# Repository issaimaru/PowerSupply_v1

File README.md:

# アズサ(Azusa)

<br>

<br>
この基板はJLCPCB様のFree PCB Sponsorshipにて制作しています．<br>

## Overview
  [MotorDriver-Controller_v4](https://github.com/TNCT-Mechatech/MotorDriver-Controller_v4)の機能+αと電源回路を合体させた統合型電源基板<br>
 
## Environments
&emsp;
&emsp;&emsp;
<br>

## Usage

1. [DriveUnit Bseries](https://github.com/Issaimaru/MoterDriver_v1)を使用したいチャネルのカードエッジコネクタに差し込む．<br>
1. モータードライバを差し込んだエッジコネクタと同じチャネルにモータを接続し，必要に応じて同じチャネルのコネクタにロータリーエンコーダを接続する．<br>
1. 非常停止スイッチを刺したコネクタの下にあるトグルスイッチをONに，それ以外のトグルスイッチをOFFにする．
1. XT90とUSB Type-Cからそれぞれ電源を供給し，非常停止スイッチをONにすると稼働する．
> **Note**<br>
> USB Type-C用電源を省略する方法はDescriptionsを参照<br>

## Features
<dl>
  <dt>通信プロトコル</dt>
  <dd>CAN with Flexible Data Rate(CAN FD)</dd>
  <dt>通信用コネクタ・ケーブル</dt>
  <dd>RJ-45/LANケーブル</dd>
  <dt>マイクロコンピュータ</dt>
  <dd>STM32F446RE</dd>
  <dt>特殊回路</dt>
  <dd>
  ・オートディスチャージ回路<br>
  ・車載用スローブローヒューズ

  <dt>保護回路(電源側)</dt>
  <dd>
  ・過電流保護(閾値可変)<br>
  ・ヒステリシス付き過熱保護<br>
  ・短絡保護<br>
  ・突入電流抑制<br>
  </dd>
  <dt>保護回路(信号側)</dt>
  <dd>
  ・過電圧保護<br>
  ・過電圧クランプ<br>
  ・突入電流抑制<br>
  ・過電流保護(東芝のeFuseを使用)<br>
  ・過熱保護<br>

## Descriptions
本ハードウェアの使用方法を詳しく書いていきます．<br>
質問や連絡等あれば[@TakenMaker](https://twitter.com/TakenMaker)までお願いします．<br>

### 回路図
&ensp;&ensp;

#### 始動方法
始動方法については[Usage](#usage)で示しました．<br>
ここでは始動時の応用的な使い方について紹介していきます．

- 信号用バッテリーの省略

<br>

JP6で信号用の電源をUSB給電or外部給電に切り替えることができます．<br>
外部電源としては，SPOWのピンに接続された電源かリポバッテリーか選ぶことができます．<br>
リポバッテリーの場合は「GND」と「SPOW」のピンヘッダを短絡してください．<br>
その際にE5VのLEDが点灯していることを確認してください．

## Bills of materials
> **Note**<br>
>最低限の部品のみここに書いています．<br>
>はんだ付けに必要な部品を調べるときは以下のexcelファイルを見るか，BOMファイルを出力してください．<br>
>[アズサ(Azusa)-ver2.0_必要部品.xlsx](src/%E3%82%A2%E3%82%BA%E3%82%B5(Azusa)-ver2.0_%E5%BF%85%E8%A6%81%E9%83%A8%E5%93%81.xlsx)
<br>
<dl>
  <dt>マイクロコンピュータ</dt>
  <dd>

  [STM32F446RET6](https://www.digikey.jp/ja/products/detail/stmicroelectronics/STM32F446RET6/5175962)

  </dd>

  <dt>電流センサ</dt>
  <dd>
  
  [CZ-3A04](https://www.digikey.jp/ja/products/detail/asahi-kasei-microdevices-akm/CZ3A04/11570562)

  </dd>
  <dt>CANトランシーバ</dt>
  <dd>

  [MCP2558FDT-H/MNY](https://www.digikey.jp/ja/products/detail/microchip-technology/MCP2558FDT-H-MNY/6009304)

  </dd>
  <dt>CANコントローラ</dt>
  <dd>

  [MCP2517FDT-H/SL](https://www.digikey.jp/ja/products/detail/microchip-technology/MCP2517FDT-H-SL/7801797)

  </dd>
  <dt>ヒートシンク</dt>
  <dd>
  
  [V2020B](https://www.digikey.jp/ja/products/detail/assmann-wsw-components/V2020B/8826902)
  
  </dd>
  <dt>ヒューズ</dt>
  <dd>

  [0297030.WXT](https://www.digikey.jp/en/products/detail/littelfuse-inc/0297030-WXT/5233697)

  </dd>
  <dt>USB・シリアル変換IC</dt>
  <dd>

  [CH340E](https://akizukidenshi.com/catalog/g/gI-13543/)

  </dd>
  <dt>NTCサーミスタ</dt>
  <dd>

  [NCU15WB473F60RC](https://www.digikey.jp/ja/products/detail/murata-electronics/NCU15WB473F60RC/9686720)

  </dd>
  <dt>DIPスイッチ</dt>
  <dd>

  [RDS-16S-1055-SMT-TR](https://www.digikey.jp/ja/products/detail/cui-devices/RDS-16S-1055-SMT-TR/12424507)

  </dd>
</dl>

## Contact
- Twitter [@TakenMaker](https://twitter.com/TakenMaker)

## Author
    
<table>
  <tr>
    <td align="center"><a href="https://github.com/Issaimaru"><br /></a>Issaimaru</td>
  </tr>
</table>
    
## Licence
  - Copyright © 2022-2023 Issaimaru<br>

本ハードウェアは，Apache License Version 2.0の下で配布されます．<br>
詳しくはLICENSEファイルをご確認ください．<br>

## 回路図のダウンロード(クローン)方法
1. Gitをインストールする．<br>Gitのインストール方法は[ここ](https://www.sejuku.net/blog/73444)を参照．
1. コマンドプロンプトを立ち上げる．
1. `cd ”ダウンロード先フォルダの絶対パス” `<br>
1. `git clone https://github.com/Issaimaru/PowerSupply_v1.git`<br>

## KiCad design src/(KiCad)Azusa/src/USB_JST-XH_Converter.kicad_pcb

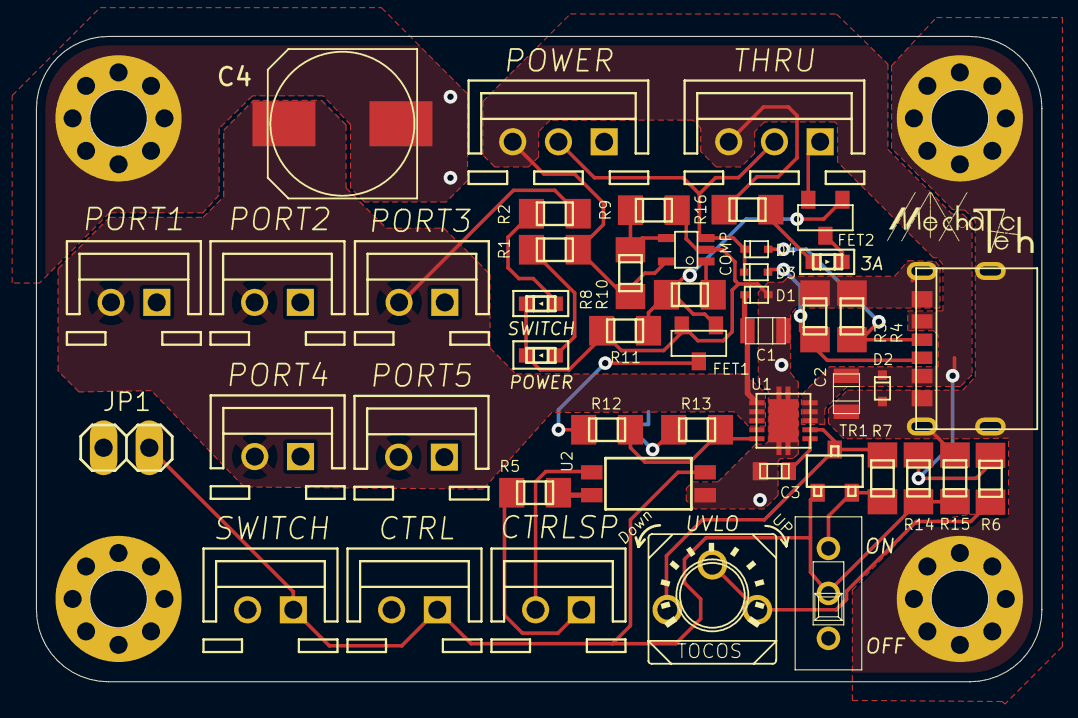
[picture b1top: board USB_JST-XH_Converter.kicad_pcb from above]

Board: 2 copper layers, 55.9 x 35.9 mm, 51 parts (0 on the bottom side), 22 nets.

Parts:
C1, C2: GRM21BC72A105KE01
C3: GRM1885C1H242JA01D; GRM18
C4: UWT1E221MNL1GS
COMP1: MCP6541T-I_LT; SC-70-5
CTRL: 02-JST; B2B-XH
CTRLSP: 02-JST; B2B-XH
D1, D3, D4: RB751S40; SOD-523
D2: PJSD12TS; SOD-523
FET1, FET2: BSS138; SOT-23
H1, H2, H3, H4: MOUNT-HOLE3.2(NORESIST); 3,2
JP1: PINHD-1X2; 1X02
LED1: SML-E12V8WT86
PORT1, PORT2, PORT3, PORT4, PORT5: 02-JST; B2B-XH
POW1: SML-E12V8WT86
POWER: 03-JST; B3B-XH
R1, R2: RG2012N-101-B-T5; RG2012
R3, R4: 5.1k; RG2012
R5: 1k; RG2012
R6, R8, R13#2, R14: 10k; RG2012
R7: 3k; RG2012
R9: 2.7k; RG2012
R12: 69.8k; RG2012
R12#2: 10; RG2012
R13: 75k; RG2012
R16: 100k; RG2012
R18: 100; RG2012
SW1: SS-12D00G3
SW2: SML-E12V8WT86
SWITCH: 02-JST; B2B-XH
THRU: 03-JST; B3B-XH
TP1: GF063PB302K; GF063PB104K
TR1: 2SC3325
U1: TCKE805NAWSON10B_TOS-REC; WSON10B_TOS-RIC
U2: TLP293; SO4_TOS
USB1: UJC-HP-3-SMT-TR

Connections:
CC: COMP1.IN+, D3.C, D4.C, POWER.2, THRU.2
CC1: D3.A, R3.LEFT, USB1.A5
CC2: D4.A, R4.LEFT, USB1.B5
GND: C1.P$2, C2.P$2, C3.R, C4.C, COMP1.VSS, D1.A, D2.A, FET1.S, FET2.S, H1.P$1, H2.P$1, H3.P$1, H4.P$1, JP1.2, PORT1.1, PORT2.1, PORT3.1, PORT4.1, PORT5.1, POW1.K, POWER.1, R3.RIGHT, R4.RIGHT, R7.LEFT, R9.RIGHT, R13.RIGHT, R13#2.RIGHT, R16.RIGHT, SW1.R, SW2.K, SWITCH.2, THRU.1, TR1.E, U1.GND1, U1.GND2, U1.GND3, U1.GND4, U1.GND5, U2.3, USB1.A12, USB1.B12, USB1.SHIELD1, USB1.SHIELD2, USB1.SHIELD3, USB1.SHIELD4
ILIM: R12.LEFT, R13.LEFT, U1.ILIM
unnamed: C3.L, U1.DVDT
unnamed: COMP1.IN-, R8.LEFT, R9.LEFT
unnamed: COMP1.OUT, R12#2.RIGHT
unnamed: CTRLSP.1, R5.RIGHT
unnamed: CTRLSP.2, U2.1
unnamed: FET1.D, R12.RIGHT
unnamed: FET2.D, LED1.K
unnamed: LED1.A, R18.RIGHT
unnamed: POW1.A, R1.LEFT
unnamed: R2.LEFT, SW2.A
unnamed: R5.LEFT, U2.2
unnamed: R6.LEFT, TP1.CENTER, TP1.RIGHT
unnamed: R7.RIGHT, TP1.LEFT, TR1.C, U1.EN/UVLO
OUT: FET1.G, FET2.G, R12#2.LEFT, R13#2.LEFT
SWITCH: CTRL.1, JP1.1, R14.LEFT, R16.LEFT, SW1.C, SWITCH.1, TR1.B, U2.4
VCC: C1.P$1, C4.A, D1.C, PORT1.2, PORT2.2, PORT3.2, PORT4.2, PORT5.2, R2.RIGHT, U1.VOUT1, U1.VOUT2, U1.VOUT3
VCC_P: C2.P$1, COMP1.VDD, D2.C, POWER.3, R1.RIGHT, R6.RIGHT, R8.RIGHT, R14.RIGHT, R18.LEFT, THRU.3, U1.VIN1, U1.VIN2, U1.VIN3, USB1.A9, USB1.B9

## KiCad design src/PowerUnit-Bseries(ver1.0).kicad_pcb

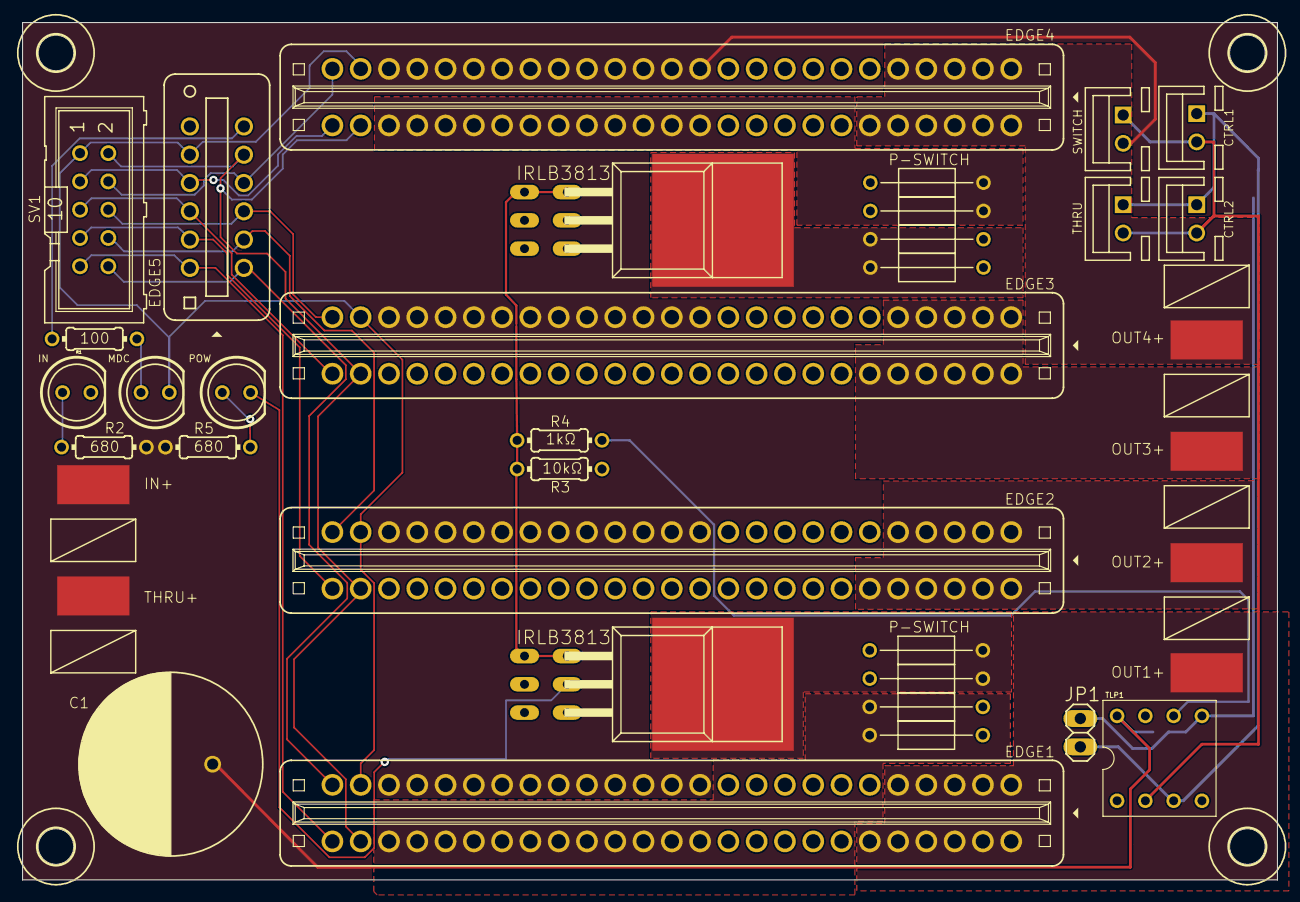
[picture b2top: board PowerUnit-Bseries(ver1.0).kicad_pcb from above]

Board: 2 copper layers, 112.7 x 77.0 mm, 50 parts (0 on the bottom side), 37 nets.

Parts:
C1: 50ZLH1000MEFC16X25
C2: GCM188L81H104KA57
CTRL1, CTRL2: 02-JST; B2B-XH
EDGE1, EDGE2, EDGE3, EDGE4: 10046971-019LF-FEMAL; 10046971-019LF
EDGE5: 7-5530843-6
H1, H2, H3, H4: MOUNT-HOLE3.2; 3,2
IN+: PADS14; AWG14
IN-: PADS14; AWG14
IRLB3813, IRLB3813#2, IRLB3813#3, IRLB3813#4: IRLB3813_2; TO-220AB-PUT
JP1: PINHD-1X2; 1X02
LED1, LED2, LED3: LED5MM
OUT1+, OUT1-, OUT2+, OUT2-, OUT3+, OUT3-, OUT4+, OUT4-: PADS14; AWG14
P-1, P-2, P-3, P-4, P-5, P-6, P-7, P-8: P-SWITCH
R1: 100; 0204_7
R2, R5: 680; 0204_7
R3: 1kΩ; 0204_7
R4: 10kΩ; 0204_7
SV1: ML10
SWITCH: 02-JST; B2B-XH
THRU: 02-JST; B2B-XH
THRU+: PADS14; AWG14
THRU-: PADS14; AWG14
TLP1: 2227MC-08-03

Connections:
/DIR1: EDGE1.P$26, EDGE5.P$12, SV1.9
/DIR2: EDGE2.P$26, EDGE5.P$11, SV1.7
/DIR3: EDGE3.P$26, EDGE5.P$10, SV1.5
/DIR4: EDGE4.P$26, EDGE5.P$9, SV1.3
/GND2: EDGE1.P$24, EDGE2.P$24, EDGE3.P$24, EDGE4.P$24, EDGE5.P$8, LED2.K, SV1.1
/LED: EDGE5.P$6, R1.1
/PWM1: EDGE1.P$25, EDGE5.P$1, SV1.10
/PWM2: EDGE2.P$25, EDGE5.P$2, SV1.8
/PWM3: EDGE3.P$25, EDGE5.P$3, SV1.6
/PWM4: EDGE4.P$25, EDGE5.P$4, SV1.4
/VCC2: EDGE1.P$27, EDGE2.P$27, EDGE3.P$27, EDGE4.P$27, EDGE5.P$5, SV1.2
GND: C1.C, C2.P$2, IN-.P$1, IRLB3813.S, IRLB3813#2.S, IRLB3813#3.S, IRLB3813#4.S, JP1.1, LED1.K, R4.2, THRU-.P$1, TLP1.P$5
unnamed: CTRL1.1, CTRL2.1, JP1.2, THRU.1, TLP1.P$3
unnamed: CTRL1.2, CTRL2.2, SWITCH.1, THRU.2, TLP1.P$2
unnamed: EDGE1.P$1, EDGE1.P$2, EDGE1.P$3, EDGE1.P$4, EDGE1.P$5, EDGE1.P$45, EDGE1.P$46, EDGE1.P$47, EDGE1.P$48, EDGE1.P$49, EDGE1.P$50, OUT1+.P$1
unnamed: EDGE1.P$6, EDGE1.P$7, EDGE1.P$8, EDGE1.P$9, EDGE1.P$10, EDGE1.P$11, EDGE1.P$40, EDGE1.P$41, EDGE1.P$42, EDGE1.P$43, EDGE1.P$44, OUT1-.P$1
unnamed: EDGE1.P$28, EDGE1.P$29, EDGE1.P$30, EDGE1.P$31, EDGE1.P$32, EDGE1.P$33, EDGE1.P$34, EDGE1.P$35, EDGE1.P$36, EDGE1.P$37, EDGE1.P$38, EDGE1.P$39, P-1.P$1, P-2.P$1
unnamed: EDGE2.P$1, EDGE2.P$2, EDGE2.P$3, EDGE2.P$4, EDGE2.P$5, EDGE2.P$45, EDGE2.P$46, EDGE2.P$47, EDGE2.P$48, EDGE2.P$49, EDGE2.P$50, OUT2+.P$1
unnamed: EDGE2.P$6, EDGE2.P$7, EDGE2.P$8, EDGE2.P$9, EDGE2.P$10, EDGE2.P$11, EDGE2.P$40, EDGE2.P$41, EDGE2.P$42, EDGE2.P$43, EDGE2.P$44, OUT2-.P$1
unnamed: EDGE2.P$28, EDGE2.P$29, EDGE2.P$30, EDGE2.P$31, EDGE2.P$32, EDGE2.P$33, EDGE2.P$34, EDGE2.P$35, EDGE2.P$36, EDGE2.P$37, EDGE2.P$38, EDGE2.P$39, P-3.P$1, P-4.P$1
unnamed: EDGE3.P$1, EDGE3.P$2, EDGE3.P$3, EDGE3.P$4, EDGE3.P$5, EDGE3.P$45, EDGE3.P$46, EDGE3.P$47, EDGE3.P$48, EDGE3.P$49, EDGE3.P$50, OUT3+.P$1
unnamed: EDGE3.P$6, EDGE3.P$7, EDGE3.P$8, EDGE3.P$9, EDGE3.P$10, EDGE3.P$11, EDGE3.P$40, EDGE3.P$41, EDGE3.P$42, EDGE3.P$43, EDGE3.P$44, OUT3-.P$1
unnamed: EDGE3.P$28, EDGE3.P$29, EDGE3.P$30, EDGE3.P$31, EDGE3.P$32, EDGE3.P$33, EDGE3.P$34, EDGE3.P$35, EDGE3.P$36, EDGE3.P$37, EDGE3.P$38, EDGE3.P$39, P-5.P$1, P-6.P$1
unnamed: EDGE4.P$1, EDGE4.P$2, EDGE4.P$3, EDGE4.P$4, EDGE4.P$5, EDGE4.P$45, EDGE4.P$46, EDGE4.P$47, EDGE4.P$48, EDGE4.P$49, EDGE4.P$50, OUT4+.P$1
unnamed: EDGE4.P$6, EDGE4.P$7, EDGE4.P$8, EDGE4.P$9, EDGE4.P$10, EDGE4.P$11, EDGE4.P$40, EDGE4.P$41, EDGE4.P$42, EDGE4.P$43, EDGE4.P$44, OUT4-.P$1
unnamed: EDGE4.P$28, EDGE4.P$29, EDGE4.P$30, EDGE4.P$31, EDGE4.P$32, EDGE4.P$33, EDGE4.P$34, EDGE4.P$35, EDGE4.P$36, EDGE4.P$37, EDGE4.P$38, EDGE4.P$39, P-7.P$1, P-8.P$1
unnamed: IRLB3813.G, IRLB3813#2.G, IRLB3813#3.G, IRLB3813#4.G, R3.2, R4.1
unnamed: IRLB3813.P$1, P-1.P$2, P-2.P$2
unnamed: IRLB3813#2.D, LED3.K
unnamed: IRLB3813#2.P$1, P-3.P$2, P-4.P$2
unnamed: IRLB3813#3.P$1, P-5.P$2, P-6.P$2
unnamed: IRLB3813#4.P$1, P-7.P$2, P-8.P$2
unnamed: LED1.A, R2.1
unnamed: LED2.A, R1.2
unnamed: LED3.A, R5.1
unnamed: R3.1, TLP1.P$6
VCC: C1.A, C2.P$1, EDGE1.P$12, EDGE1.P$13, EDGE1.P$14, EDGE1.P$15, EDGE1.P$16, EDGE1.P$17, EDGE1.P$18, EDGE1.P$19, EDGE1.P$20, EDGE1.P$21, EDGE1.P$22, EDGE1.P$23, EDGE2.P$12, EDGE2.P$13, EDGE2.P$14, EDGE2.P$15, EDGE2.P$16, EDGE2.P$17, EDGE2.P$18, EDGE2.P$19, EDGE2.P$20, EDGE2.P$21, EDGE2.P$22, EDGE2.P$23, EDGE3.P$12, EDGE3.P$13, EDGE3.P$14, EDGE3.P$15, EDGE3.P$16, EDGE3.P$17, EDGE3.P$18, EDGE3.P$19, EDGE3.P$20, EDGE3.P$21, EDGE3.P$22, EDGE3.P$23, EDGE4.P$12, EDGE4.P$13, EDGE4.P$14, EDGE4.P$15, EDGE4.P$16, EDGE4.P$17, EDGE4.P$18, EDGE4.P$19, EDGE4.P$20, EDGE4.P$21, EDGE4.P$22, EDGE4.P$23, IN+.P$1, R2.2, R5.2, SWITCH.2, THRU+.P$1, TLP1.P$8

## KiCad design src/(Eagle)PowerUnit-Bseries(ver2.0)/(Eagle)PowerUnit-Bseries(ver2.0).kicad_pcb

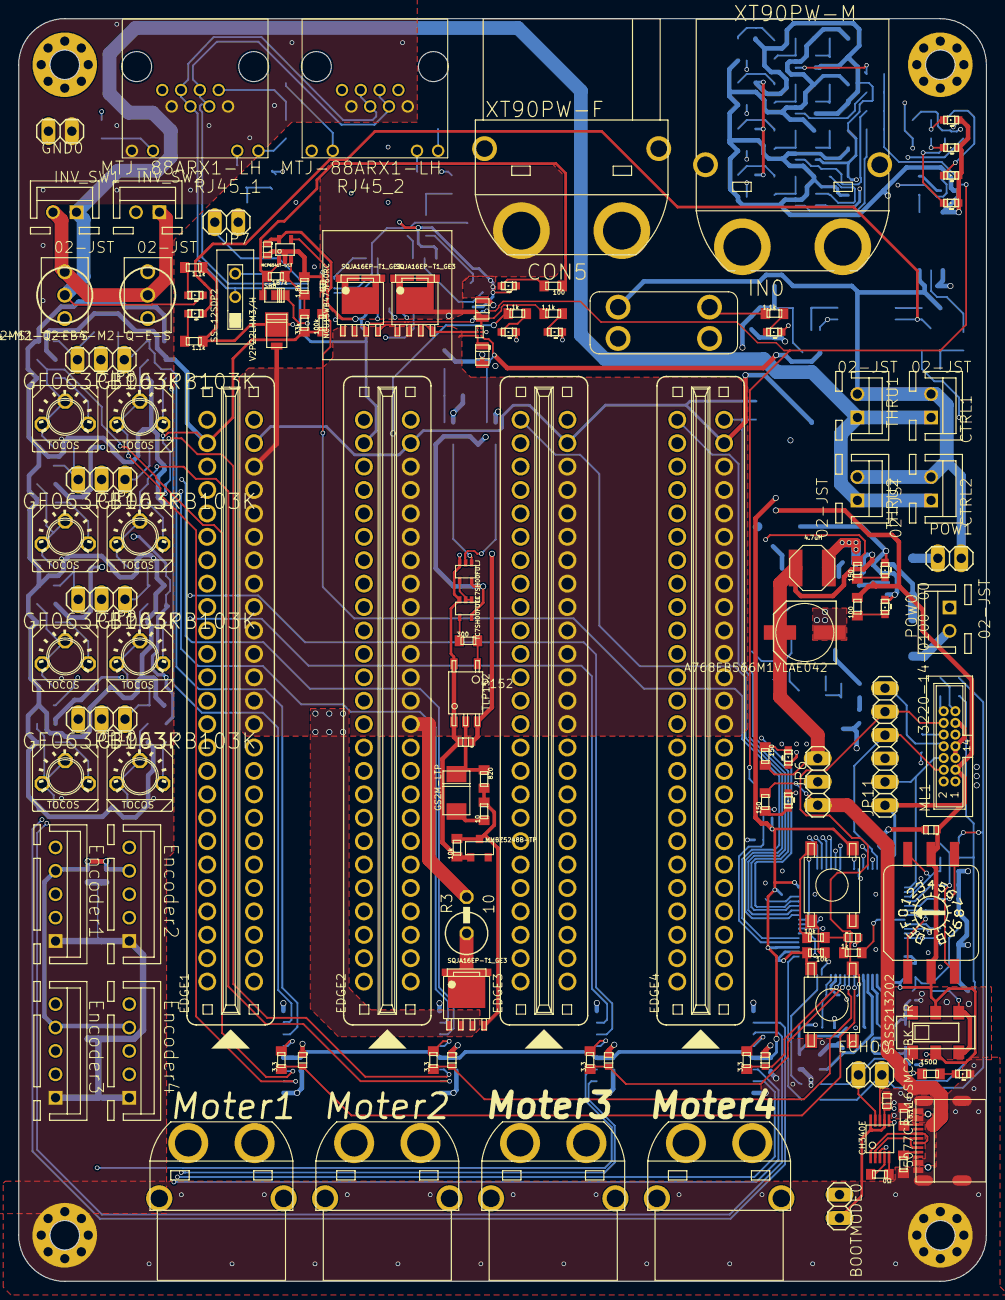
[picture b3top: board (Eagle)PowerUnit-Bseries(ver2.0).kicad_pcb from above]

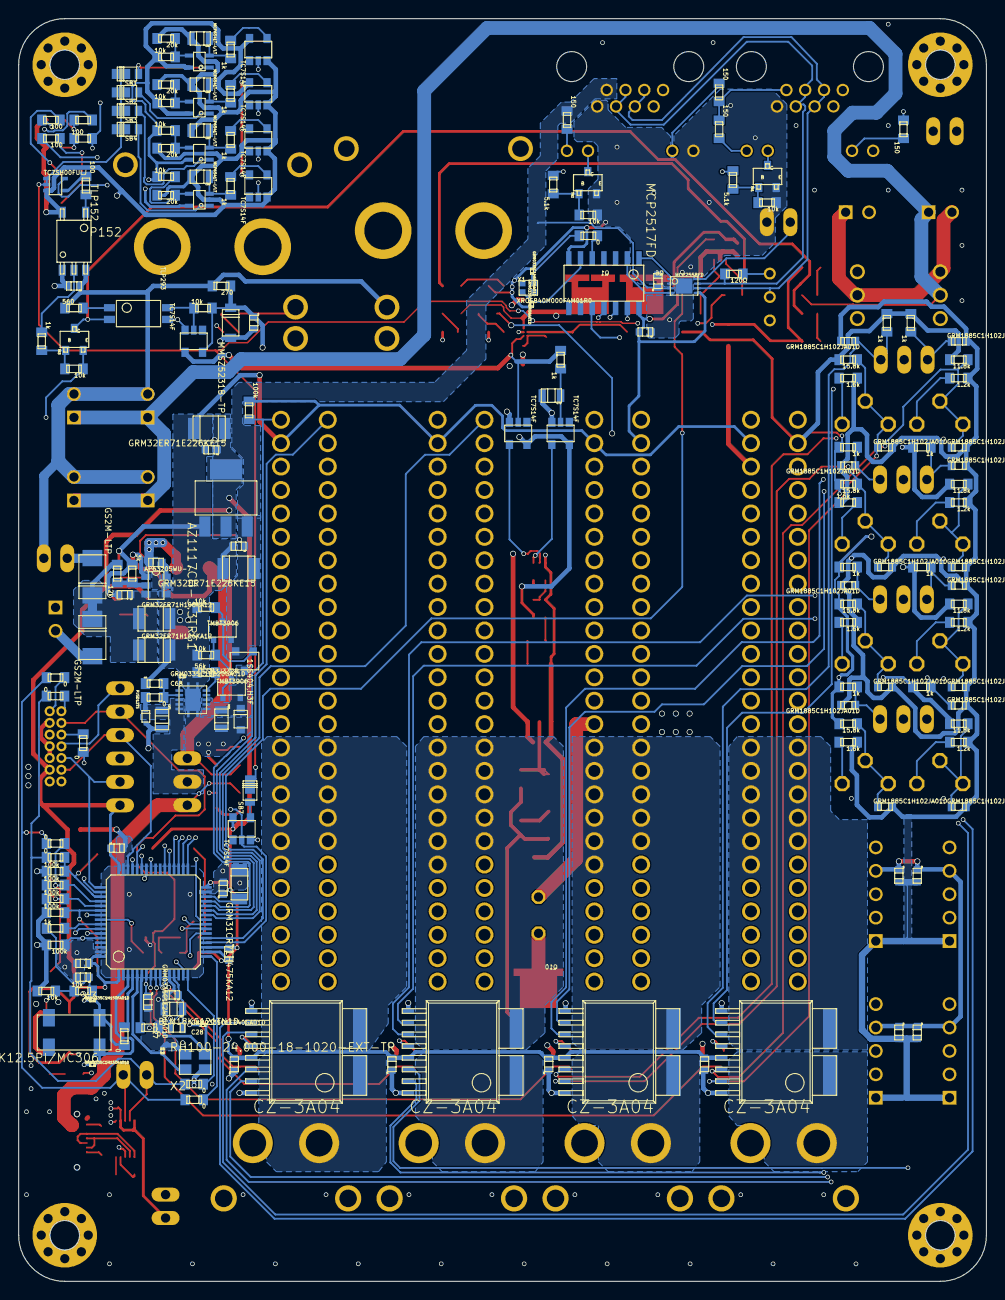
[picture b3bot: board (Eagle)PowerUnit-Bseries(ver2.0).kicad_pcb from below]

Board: 4 copper layers, 105.0 x 137.0 mm, 315 parts (187 on the bottom side), 207 nets.

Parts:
B1: CS11029.5F100
B2: PTS645SM95SMTR92LFS
BOOTMODE0: 1X02
C2, C23, C47, C50, C53, C56, C66, C67, C69, C71: GRM21BC72A105KE01
C3, C6, C8, C10, C11, C13, C14, C15, C18, C19, C20, C21, C22, C26, C31, C32, C33, C34, C35, C36, C37, C38, C43, C46, C57, C60, C61, C64, C65, C70, C72, C73: GCM188L81H104KA57
C4, C5: GRM32ER71H106KA12
C7: A768EB566M1VLAE042
C9, C12: GRM32ER71E226KE15; 3225M
C16, C17: GRM0335C1H6R0BA01D; GRM0335C1H120GA01
C24: GRM31CR71H475KA12
C27, C28: GRM0335C1E240GA01D
C29, C30: GRM0335C1H150FA01D; GRM0335C1H120GA01
C39, C40, C41, C42, C44, C45, C48, C49, C51, C52, C54, C55, C58, C59, C62, C63: GRM1885C1H102JA01D; GRM18
C68: GRM0335C1H620GA01D; GRM0335C1E240GA01D
CON4: XT60PW-F
CON5: XT90PW-F
CTRL1, CTRL2: 02-JST; B2B-XH
D1, D2, D4: GS2M-LTP
D3: PJSD12TS; SOD-523
ECHO0: 1X02
EDGE1, EDGE2, EDGE3, EDGE4: 10046971-019LF-FEMAL; 10046971-019LF
Encoder1, Encoder2, Encoder3, Encoder4: B5B-XH
FB1: BLM18KG121TN1D
FUSE1: FUSEHOLDER-3568
GND0: 1X02
H1, H2, H3, H4: MOUNT-HOLE3.2(NORESIST); 3,2
HEATSINK1: V2020B
IN0: XT90PW-M
INV_SW1, INV_SW2: 02-JST; B2B-XH
JP1, JP6, JP8, JP9, JP10: 1X03
JP7: 1X02
JP11: 1X06
L1: 4.7uH; NRS5030T4R7MMGJ
LED1, LED2, LED3, LED5, LED6, LED7, LED8, LED9, LED10, LED11, LED12, LED13, LED14, LED15: SML-E12V8WT86
LED4: SMLE13BC8T; SML-E12V8WT86
ML1: 3220-14-0100-00
MOTER: XT60PW-F
Moter1, Moter3: XT60PW-F
NTC1: NCU15WB473F60RC
POW0: 02-JST; B2B-XH
POW1: 1X02
Q1, Q6, Q10: SQJA16EP-T1_GE3
Q2: SSM3J332R; SOT-23F
Q11, Q12: TMBT3906
R1, R67, R99, R104: 11.8k; CR0603
R2, R5, R79, R113, R116: 1.1k; CR0603
R3: 10; 0411V
R4: 560; CR0603
R6: 820; CR0603
R7: 120Ω; CR0603
R8, R9, R39, R40: 5.1k; CR0603
R10: 150Ω; CR0603
R11, R15, R29, R30, R31, R41, R82: 100k; CR0603
R12, R20, R21, R37, R38, R45, R46, R48, R49, R60, R65, R71, R115, R119, R121: 10k; CR0603
R13, R34, R35, R36, R86, R87, R89: 150; CR0603
R14, R16, R17, R25, R26, R27, R28, R51, R52, R53, R74: 0; CR0603
R18: 12k; CR0603
R19: 3k; CR0603
R22, R61, R66, R72: 20k; CR0603
R23, R24, R33, R47, R50, R58, R59, R62, R63, R64, R68, R69, R70, R73, R77, R120: 1k; CR0603
R32: 10; CR0603
R42, R43, R44, R78, R85, R88, R90: 100; CR0603
R54, R95, R100, R105: 1.2k; CR0603
R55, R96, R101, R106: 15.8k; CR0603
R56, R97, R102, R107: 1.6k; CR0603
R57, R98, R103, R108: 3.3; CR0603
R75: ∞; CR0603
R76: 56k; CR0603
R80: 33k; CR0603
R81: 1.8k; CR0603
R83: 187k; CR0603
R84: 0Ω; CR0603
R122: 300; CR0603
R123: 270; CR0603
RJ45_1, RJ45_2: MTJ-88ARX1-LH
SB1, SB2, SB3, SB4, SB7, SB8: RSX101VAM-30TR
SB5: V2P22LHM3/H; V2P22LHM3_H
SB6: 1SS404,H3F
SW1: SS-12SDP2
SW2: RDS-16S-1055-SMT-TR
SW3: SSSS213202
SW4, SW5: 2MS1-T2-B4-M2-Q-E-S
THRU1, THRU2: 02-JST; B2B-XH
TLP1, TLP3: TLP152
TP1, TP2, TP3, TP4, TP5, TP6, TP7, TP8: GF063PB103K; GF063PB104K
TR1, TR2, TR3: 2SC3325
U1: LQFP64; STM32F446XC
U2: MCP2517FD
U3: CH340E; MSOP-10
U4, U6, U8, U9: CZ-3A04; CZ3A07
U5: AP63205WU-7; AP63203WU-7
U7, U11, U12, U24, U27: MCP6541T-I/LT; SC-70-5
U10, U13, U17, U18, U21, U22, U23, U25: TC7S14F
U14: TCK420G
U15: TCKE805NAWSON10B_TOS-REC; WSON10B_TOS-RIC
U16, U19, U26: TC7SH00FULJ; SSOP5-P-0.65A
U20: TLP293
U$1: MCP2558FD
U$4: AZ1117CH-3.3TRG1; AZ1117C
USB1: 5077CR-16SMC2-BK-TR
X1: XRCGB40M000F4M01R0; XRCGB40M000F4M00R0
X2: RH100-24.000-18-1020-EXT-TR
X3: 32.768K12.5PI/MC306; 32.768K12.5PI_MC306
ZD1: MMSZ5231B-TP
ZD5: MMBZ5248B-TP

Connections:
5V1: C73.P$1, R121.RIGHT, R123.LEFT, U16.VCC, U17.VCC, U18.VCC, U19.VCC, U21.VCC, ZD1.CATHODE
+3V3: B2.1, BOOTMODE0.2, C3.P$2, C11.P$1, C12.L, C13.P$2, C15.P$1, C18.P$1, C19.P$1, C20.P$1, C21.P$1, C37.P$2, C38.P$2, C57.P$2, C61.P$2, C72.P$1, EDGE1.P$27, EDGE2.P$27, EDGE3.P$27, EDGE4.P$27, FB1.1, JP11.1, ML1.3, R1.RIGHT, R21.LEFT, R24.RIGHT, R33.RIGHT, R55.RIGHT, R58.RIGHT, R59.RIGHT, R60.LEFT, R63.RIGHT, R64.RIGHT, R65.LEFT, R67.RIGHT, R69.RIGHT, R70.RIGHT, R71.LEFT, R80.LEFT, R82.LEFT, R88.RIGHT, R96.RIGHT, R99.RIGHT, R101.RIGHT, R104.RIGHT, R106.RIGHT, SW2.C1, SW2.C2, SW3.2A, SW3.2B, U1.P1, U1.P19, U1.P32, U1.P48, U1.P64, U2.VDD, U3.3V3, U3.VCC, U4.VDD, U6.VDD, U7.VDD, U8.VDD, U9.VDD, U10.VCC, U11.VDD, U12.VDD, U13.VCC, U22.VCC, U23.VCC, U24.VDD, U25.VCC, U26.VCC, U27.VDD, U$1.VIO, U$4.OUTPUT, U$4.VOUT
+5V: C9.L, C10.P$1, C14.P$1, C31.P$1, C32.P$1, C33.P$1, C34.P$1, Encoder1.4, Encoder2.4, Encoder3.4, Encoder4.4, Q2.S, Q11.E, R13.RIGHT, R34.RIGHT, R35.LEFT, R36.LEFT, R89.RIGHT, RJ45_1.1, RJ45_1.7, RJ45_2.1, RJ45_2.7, U$1.VDD, U$4.INPUT
ALIVE_LED: R42.RIGHT, U1.P45
BOOT0: BOOTMODE0.1, R11.LEFT, U1.P60
CAN_H: R7.RIGHT, RJ45_1.5, RJ45_1.6, RJ45_2.5, RJ45_2.6, U$1.CANH
CAN_L: RJ45_1.3, RJ45_1.4, RJ45_2.3, RJ45_2.4, SW1.C, U$1.CANL
COM_LED: R39.RIGHT, R40.RIGHT, R43.RIGHT, U1.P44
CS: U1.P33, U2.NCS
CS1_OCD1: C44.L, JP8.3, R58.LEFT, U4.OCD1
CS1_OCD2: C45.L, JP8.1, R59.LEFT, U4.OCD2
CS1_REF1: C41.L, R1.LEFT, TP1.CENTER, TP1.LEFT, U4.REF1
CS1_REF2: C42.L, R55.LEFT, TP2.CENTER, TP2.LEFT, U4.REF2
CS2_OCD1: C48.L, JP1.3, R24.LEFT, U6.OCD1
CS2_OCD2: C49.L, JP1.1, R33.LEFT, U6.OCD2
CS2_REF1: C39.L, R67.LEFT, TP3.CENTER, TP3.LEFT, U6.REF1
CS2_REF2: C40.L, R96.LEFT, TP4.CENTER, TP4.LEFT, U6.REF2
CS3_OCD1: C51.L, JP9.3, R63.LEFT, U8.OCD1
CS3_OCD2: C52.L, JP9.1, R64.LEFT, U8.OCD2
CS3_REF1: C58.L, R99.LEFT, TP5.CENTER, TP5.LEFT, U8.REF1
CS3_REF2: C59.L, R101.LEFT, TP6.CENTER, TP6.LEFT, U8.REF2
CS4_OCD1: C54.L, JP10.3, R69.LEFT, U9.OCD1
CS4_OCD2: C55.L, JP10.1, R70.LEFT, U9.OCD2
CS4_REF1: C62.L, R104.LEFT, TP7.CENTER, TP7.LEFT, U9.REF1
CS4_REF2: C63.L, R106.LEFT, TP8.CENTER, TP8.LEFT, U9.REF2
CURRENT1: C43.P$2, R57.LEFT, U1.P8
CURRENT2: C46.P$2, R98.LEFT, U1.P9
CURRENT3: C60.P$2, R103.LEFT, U1.P10
CURRENT4: C64.P$2, R108.LEFT, U1.P11
DEBUG_BT: R47.RIGHT, U1.P56
DEBUG_LED: R44.RIGHT, U1.P43
DEBUG_SW: R50.RIGHT, U1.P57
DIP_SW1: R41.RIGHT, SW2.1, U1.P54
DIP_SW2: R31.RIGHT, SW2.2, U1.P53
DIP_SW3: R25.RIGHT, R30.RIGHT, SW2.4, U1.P52
DIP_SW4: R26.RIGHT, R29.RIGHT, SW2.8, U1.P51
DIR1: EDGE1.P$26, U1.P24
DIR2: EDGE2.P$26, U1.P25
DIR3: EDGE3.P$26, U1.P26
DIR4: EDGE4.P$26, U1.P27
DISABLE: R90.RIGHT, U1.P20, U22.IN
E5V: C7.ANODE, JP6.3, L1.R, R86.RIGHT, U5.FB
EMERGENCY: R120.RIGHT, U14.VCT, U18.IN, U21.OUT
ENC1_A: Encoder1.3, U1.P41
ENC1_B: Encoder1.5, U1.P42
ENC2_A: Encoder2.3, U1.P22
ENC2_B: Encoder2.5, U1.P23
ENC3_A: Encoder3.3, U1.P58
ENC3_B: Encoder3.5, U1.P59
ENC4_A: Encoder4.3, U1.P37
ENC4_B: Encoder4.5, U1.P38
IN1: EDGE1.P$6, EDGE1.P$7, EDGE1.P$8, EDGE1.P$9, EDGE1.P$10, EDGE1.P$11, EDGE1.P$40, EDGE1.P$41, EDGE1.P$42, EDGE1.P$43, EDGE1.P$44, U4.IN
IN2: EDGE2.P$6, EDGE2.P$7, EDGE2.P$8, EDGE2.P$9, EDGE2.P$10, EDGE2.P$11, EDGE2.P$40, EDGE2.P$41, EDGE2.P$42, EDGE2.P$43, EDGE2.P$44, U6.IN
IN3: EDGE3.P$6, EDGE3.P$7, EDGE3.P$8, EDGE3.P$9, EDGE3.P$10, EDGE3.P$11, EDGE3.P$40, EDGE3.P$41, EDGE3.P$42, EDGE3.P$43, EDGE3.P$44, U8.IN
IN4: EDGE4.P$6, EDGE4.P$7, EDGE4.P$8, EDGE4.P$9, EDGE4.P$10, EDGE4.P$11, EDGE4.P$40, EDGE4.P$41, EDGE4.P$42, EDGE4.P$43, EDGE4.P$44, U9.IN
IP1: Moter1.-, U4.IP
IP2: MOTER.-, U6.IP
IP3: Moter3.-, U8.IP
IP4: CON4.-, U9.IP
MISO: U1.P35, U2.SDO
MOSI: U1.P36, U2.SDI
unnamed: R57.RIGHT, U4.VOUT
unnamed: R56.RIGHT, TP2.RIGHT
unnamed: LED2.A, R5.RIGHT
unnamed: EDGE1.P$1, EDGE1.P$2, EDGE1.P$3, EDGE1.P$4, EDGE1.P$5, EDGE1.P$45, EDGE1.P$46, EDGE1.P$47, EDGE1.P$48, EDGE1.P$49, EDGE1.P$50, Moter1.+
unnamed: EDGE2.P$1, EDGE2.P$2, EDGE2.P$3, EDGE2.P$4, EDGE2.P$5, EDGE2.P$45, EDGE2.P$46, EDGE2.P$47, EDGE2.P$48, EDGE2.P$49, EDGE2.P$50, MOTER.+
unnamed: EDGE3.P$1, EDGE3.P$2, EDGE3.P$3, EDGE3.P$4, EDGE3.P$5, EDGE3.P$45, EDGE3.P$46, EDGE3.P$47, EDGE3.P$48, EDGE3.P$49, EDGE3.P$50, Moter3.+
unnamed: LED8.A, R116.RIGHT
unnamed: R74.LEFT, R75.RIGHT, U15.EN/UVLO
unnamed: JP8.2, U10.IN
unnamed: CON4.+, EDGE4.P$1, EDGE4.P$2, EDGE4.P$3, EDGE4.P$4, EDGE4.P$5, EDGE4.P$45, EDGE4.P$46, EDGE4.P$47, EDGE4.P$48, EDGE4.P$49, EDGE4.P$50
unnamed: Q10.D, R3.1
unnamed: R77.LEFT, TLP1.VO
unnamed: R54.RIGHT, TP1.RIGHT
unnamed: R77.RIGHT, R115.RIGHT, TR3.B
unnamed: LED8.K, TR3.C, U20.CATHODE
unnamed: LED1.A, R2.RIGHT
unnamed: R60.RIGHT, R61.LEFT, U11.IN-
unnamed: INV_SW1.2, INV_SW2.1, SW4.O, SW5.P
unnamed: C67.P$1, D3.C, JP6.2, R74.RIGHT, U15.VIN1, U15.VIN2, U15.VIN3
unnamed: CTRL1.1, CTRL2.1, INV_SW1.1, LED3.K, R115.LEFT, SW4.P, THRU1.1, THRU2.1, TR3.E
unnamed: U16.INB, U17.OUT
unnamed: R7.LEFT, SW1.R
unnamed: LED3.A, R113.RIGHT
unnamed: FUSE1.R1, FUSE1.R2, IN0.+, R79.LEFT
unnamed: Q1.G, Q6.G, U14.VGATE2
unnamed: U2.TXCAN, U$1.TXD
unnamed: U2.RXCAN, U$1.RXD
unnamed: R8.RIGHT, USB1.CC2
unnamed: R9.RIGHT, USB1.CC1
unnamed: U3.UD+, USB1.DP1, USB1.DP2
unnamed: U3.UD-, USB1.DN1, USB1.DN2
unnamed: R10.RIGHT, U3.TNOW
unnamed: LED4.A, R10.LEFT
unnamed: D1.A, POW1.2
unnamed: R18.LEFT, R19.RIGHT, U5.EN
unnamed: D2.A, POW0.2
unnamed: R14.LEFT, U2.OSC2
unnamed: C17.1, U2.OSC1, X1.1
unnamed: C6.P$2, L1.L, U5.SW
unnamed: C6.P$1, U5.BST
unnamed: C16.1, R14.RIGHT, X1.2
unnamed: R21.RIGHT, R22.LEFT, U7.IN-
unnamed: R16.LEFT, U1.P16
unnamed: R17.LEFT, U1.P17
unnamed: C22.P$1, C23.P$1, FB1.2, U1.P13
unnamed: Q11.B, Q12.B, Q12.C, R12.RIGHT
unnamed: C24.1, U1.P30
unnamed: C27.2, U1.P5, X2.1
unnamed: R28.RIGHT, U1.P4
unnamed: R13.LEFT, RJ45_1.LED2_A
unnamed: R27.RIGHT, U1.P6
unnamed: R34.LEFT, RJ45_2.LED2_A
unnamed: C28.2, R27.LEFT, X2.3
unnamed: LED12.A, R87.LEFT
unnamed: C30.2, R28.LEFT, X3.1
unnamed: C29.2, U1.P3, X3.4
unnamed: LED5.A, R42.LEFT
unnamed: LED6.A, R43.LEFT
unnamed: LED7.A, R44.LEFT
unnamed: B2.4, R45.LEFT
unnamed: B2.3, R46.LEFT
unnamed: R48.LEFT, R49.LEFT, SW3.3A, SW3.3B
unnamed: ML1.13, R51.LEFT
unnamed: C36.P$1, R48.RIGHT, R50.LEFT
unnamed: ML1.14, R52.RIGHT
unnamed: ML1.10, R53.RIGHT
unnamed: JP7.2, U$1.S
unnamed: R35.RIGHT, RJ45_1.LED1_A
unnamed: R36.RIGHT, RJ45_2.LED1_A
unnamed: RJ45_1.LED1_K, TR1.C
unnamed: RJ45_2.LED1_K, TR2.C
unnamed: R38.RIGHT, R40.LEFT, TR2.B
unnamed: R37.RIGHT, R39.LEFT, TR1.B
unnamed: C69.P$1, Q2.D, Q12.E, SB6.C, U15.VOUT1, U15.VOUT2, U15.VOUT3
unnamed: C50.P$1, R62.LEFT, U11.IN+
unnamed: SB2.A, U11.OUT
unnamed: C47.P$1, R23.LEFT, U7.IN+
unnamed: R95.RIGHT, TP3.RIGHT
unnamed: R97.RIGHT, TP4.RIGHT
unnamed: R98.RIGHT, U6.VOUT
unnamed: R100.RIGHT, TP5.RIGHT
unnamed: JP1.2, U23.IN
unnamed: R65.RIGHT, R66.LEFT, U12.IN-
unnamed: C53.P$1, R68.LEFT, U12.IN+
unnamed: SB3.A, U12.OUT
unnamed: JP9.2, U13.IN
unnamed: R68.RIGHT, U13.OUT
unnamed: R71.RIGHT, R72.LEFT, U24.IN-
unnamed: C56.P$1, R73.LEFT, U24.IN+
unnamed: SB4.A, U24.OUT
unnamed: R78.LEFT, U26.OUT
unnamed: C71.P$1, R120.LEFT, U17.IN
unnamed: R4.RIGHT, U20.ANODE
unnamed: D4.C, R6.LEFT, TLP3.VO
unnamed: Q10.G, R6.RIGHT, R32.RIGHT, R119.RIGHT, ZD5.CATHODE
unnamed: SB1.A, U7.OUT
unnamed: R102.RIGHT, TP6.RIGHT
unnamed: R103.RIGHT, U8.VOUT
unnamed: R105.RIGHT, TP7.RIGHT
unnamed: R107.RIGHT, TP8.RIGHT
unnamed: R108.RIGHT, U9.VOUT
unnamed: Q2.G, Q11.C, R20.RIGHT
unnamed: C35.P$1, R46.RIGHT, R47.LEFT
unnamed: R23.RIGHT, U10.OUT
unnamed: R122.LEFT, U19.OUT
unnamed: U16.INA, U18.OUT
unnamed: U16.OUT, U19.INA, U19.INB
unnamed: R121.LEFT, U20.COLLECTOR, U21.IN
unnamed: R122.RIGHT, TLP3.ANODE
unnamed: C66.P$1, EDGE1.P$12, EDGE1.P$13, EDGE1.P$14, EDGE1.P$15, EDGE1.P$16, EDGE1.P$17, EDGE1.P$18, EDGE1.P$19, EDGE1.P$20, EDGE1.P$21, EDGE1.P$22, EDGE1.P$23, EDGE2.P$12, EDGE2.P$13, EDGE2.P$14, EDGE2.P$15, EDGE2.P$16, EDGE2.P$17, EDGE2.P$18, EDGE2.P$19, EDGE2.P$20, EDGE2.P$21, EDGE2.P$22, EDGE2.P$23, EDGE3.P$12, EDGE3.P$13, EDGE3.P$14, EDGE3.P$15, EDGE3.P$16, EDGE3.P$17, EDGE3.P$18, EDGE3.P$19, EDGE3.P$20, EDGE3.P$21, EDGE3.P$22, EDGE3.P$23, EDGE4.P$12, EDGE4.P$13, EDGE4.P$14, EDGE4.P$15, EDGE4.P$16, EDGE4.P$17, EDGE4.P$18, EDGE4.P$19, EDGE4.P$20, EDGE4.P$21, EDGE4.P$22, EDGE4.P$23, Q1.S1, Q1.S2, Q1.S3, Q6.S1, Q6.S2, Q6.S3, R3.2, R5.LEFT, SB5.A, U14.VOUT
unnamed: D4.A, R32.LEFT
unnamed: R62.RIGHT, U23.OUT
unnamed: JP10.2, U25.IN
unnamed: R73.RIGHT, U25.OUT
unnamed: R76.RIGHT, U15.ILIM
unnamed: C68.1, U15.DVDT
unnamed: R78.RIGHT, TLP1.ANODE
unnamed: SB7.A, U22.OUT
unnamed: LED9.A, R79.RIGHT
unnamed: R84.RIGHT, U3.RTS#
unnamed: R80.RIGHT, R81.LEFT, R83.LEFT, U27.IN+
unnamed: R84.LEFT, U3.CTS#
unnamed: LED10.A, R85.RIGHT
unnamed: LED11.A, R86.LEFT
unnamed: R83.RIGHT, R85.LEFT, SB8.A, U27.OUT
unnamed: LED15.A, R90.LEFT
unnamed: LED13.A, R89.LEFT
unnamed: LED14.A, R88.LEFT
NRST: B1.1, C26.P$1, JP11.5, ML1.12, U1.P7
PGND: C2.P$2, C65.P$2, C66.P$2, C70.P$2, C71.P$2, C73.P$2, CON5.-, EDGE1.P$28, EDGE1.P$29, EDGE1.P$30, EDGE1.P$31, EDGE1.P$32, EDGE1.P$33, EDGE1.P$34, EDGE1.P$35, EDGE1.P$36, EDGE1.P$37, EDGE1.P$38, EDGE1.P$39, EDGE2.P$28, EDGE2.P$29, EDGE2.P$30, EDGE2.P$31, EDGE2.P$32, EDGE2.P$33, EDGE2.P$34, EDGE2.P$35, EDGE2.P$36, EDGE2.P$37, EDGE2.P$38, EDGE2.P$39, EDGE3.P$28, EDGE3.P$29, EDGE3.P$30, EDGE3.P$31, EDGE3.P$32, EDGE3.P$33, EDGE3.P$34, EDGE3.P$35, EDGE3.P$36, EDGE3.P$37, EDGE3.P$38, EDGE3.P$39, EDGE4.P$28, EDGE4.P$29, EDGE4.P$30, EDGE4.P$31, EDGE4.P$32, EDGE4.P$33, EDGE4.P$34, EDGE4.P$35, EDGE4.P$36, EDGE4.P$37, EDGE4.P$38, EDGE4.P$39, GND0.2, H1.P$1, H2.P$1, IN0.-, INV_SW2.2, LED1.K, LED2.K, LED9.K, Q10.S1, Q10.S2, Q10.S3, R119.LEFT, SW5.O, TLP1.GND, TLP3.CATHODE, TLP3.GND, U14.GND, U16.GND, U17.GND, U18.GND, U19.GND, U20.EMITTER, U21.GND, ZD1.ANODE, ZD5.ANODE
PWM1: EDGE1.P$25, R53.LEFT, U1.P50
PWM2: EDGE2.P$25, U1.P15
PWM3: EDGE3.P$25, U1.P29
PWM4: EDGE4.P$25, R15.RIGHT, U1.P28
SCK: U1.P34, U2.SCK
SGND: B1.3, C3.P$1, C4.R, C5.R, C7.CATHODE, C8.P$2, C9.R, C10.P$2, C11.P$2, C12.R, C13.P$1, C14.P$2, C15.P$2, C16.2, C17.2, C18.P$2, C19.P$2, C20.P$2, C21.P$2, C22.P$2, C23.P$2, C24.2, C26.P$2, C27.1, C28.1, C29.1, C30.1, C31.P$2, C32.P$2, C33.P$2, C34.P$2, C35.P$2, C36.P$2, C37.P$1, C38.P$1, C39.R, C40.R, C41.R, C42.R, C43.P$1, C44.R, C45.R, C46.P$1, C47.P$2, C48.R, C49.R, C50.P$2, C51.R, C52.R, C53.P$2, C54.R, C55.R, C56.P$2, C57.P$1, C58.R, C59.R, C60.P$1, C61.P$1, C62.R, C63.R, C64.P$1, C67.P$2, C68.2, C69.P$2, C72.P$2, D3.A, EDGE1.P$24, EDGE2.P$24, EDGE3.P$24, EDGE4.P$24, Encoder1.1, Encoder2.1, Encoder3.1, Encoder4.1, GND0.1, H3.P$1, H4.P$1, JP7.1, JP11.3, LED4.K, LED5.K, LED6.K, LED7.K, LED10.K, LED11.K, LED12.K, LED13.K, LED14.K, LED15.K, ML1.5, ML1.7, ML1.11, NTC1.L, POW0.1, R8.LEFT, R9.LEFT, R11.RIGHT, R12.LEFT, R15.LEFT, R19.LEFT, R20.LEFT, R22.RIGHT, R29.LEFT, R30.LEFT, R31.LEFT, R37.LEFT, R38.LEFT, R41.LEFT, R45.RIGHT, R49.RIGHT, R54.LEFT, R56.LEFT, R61.RIGHT, R66.RIGHT, R72.RIGHT, R75.LEFT, R76.LEFT, R81.RIGHT, R95.LEFT, R97.LEFT, R100.LEFT, R102.LEFT, R105.LEFT, R107.LEFT, RJ45_1.2, RJ45_1.8, RJ45_1.LED2_K, RJ45_2.2, RJ45_2.8, RJ45_2.LED2_K, SB6.A, TLP1.CATHODE, TR1.E, TR2.E, U1.P12, U1.P18, U1.P31, U1.P47, U1.P63, U2.VSS, U3.GND, U4.VSS1, U4.VSS2, U5.GND, U6.VSS1, U6.VSS2, U7.VSS, U8.VSS1, U8.VSS2, U9.VSS1, U9.VSS2, U10.GND, U11.VSS, U12.VSS, U13.GND, U15.GND1, U15.GND2, U15.GND3, U15.GND4, U15.GND5, U22.GND, U23.GND, U24.VSS, U25.GND, U26.GND, U27.VSS, U$1.EP, U$1.VSS, U$4.GND, USB1.GND1, USB1.GND2, USB1.SHIELD1, USB1.SHIELD2, USB1.SHIELD3, USB1.SHIELD4, X2.2, X2.4
SHUTDOWN: SB1.C, SB2.C, SB3.C, SB4.C, SB7.C, SB8.C, U26.INA, U26.INB
SWCLK: JP11.2, ML1.6, U1.P49
SWDIO: JP11.4, ML1.4, U1.P46
SWO: JP11.6, ML1.8, U1.P55
THERMAL: NTC1.R, R82.RIGHT, U1.P21, U27.IN-
U5V: JP6.1, R87.RIGHT, USB1.VBUS1, USB1.VBUS2
USART_RX: ECHO0.1, R17.RIGHT, R25.LEFT, R51.RIGHT, U3.TXD
USART_TX: ECHO0.2, R16.RIGHT, R26.LEFT, R52.LEFT, U3.RXD
V+: C4.L, C5.L, C8.P$1, D1.C, D2.C, R18.RIGHT, U5.VIN
VCC: C2.P$1, C65.P$1, C70.P$1, CON5.+, CTRL1.2, CTRL2.2, FUSE1.L1, FUSE1.L2, POW1.1, Q1.D, Q6.D, R2.LEFT, R4.LEFT, R113.LEFT, R116.LEFT, R123.RIGHT, SB5.C, THRU1.2, THRU2.2, TLP1.VCC, TLP3.VCC, U14.VIN

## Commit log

2022-05-14 Create LICENSE
2022-06-18 部品の配置
2022-06-18 配線の追加
2022-06-19 ベタの追加
2022-06-21 DRCエラーの解消
2022-06-21 配線完了
2022-06-21 Update README.md
    完成予想図の追加
2022-06-21 配線完了,KiCadへの移行の前段階
2022-06-21 Update .gitignore
    KiCAD用テンプレ
2022-06-21 KiCADへの移行
2022-06-22 QRコードの拡大
2022-06-22 KiCadへの移行前 ネジ穴の追加
2022-06-22 KiCadへの移行前 ネジ穴の追加 conflictの解消
2022-06-22 KiCadへの移行 QRコードの追加
2022-06-22 .gitignoreの反映されない問題の修復
2022-06-22 Update README.md
    画像の更新
2022-06-23 .gitignoreの更新
2022-06-23 エラーの解消
2022-06-23 基板デザインの完成
2022-06-24 Update README.md
    説明の追加
2022-06-25 Update README.md
    使用電子部品，及び値段の表の追加
2022-06-25 名前の変更、ガーバ,ドリルデータの追加
2022-06-25 gerberの名前の変更
2022-06-25 再設計 Edgeコネクタを40Pにした
2022-06-25 基盤デザインの完成 gerber出力
2022-06-26 基「板」デザインの完成 gerber出力
2022-06-26 前バージョンへの移行
2022-07-06 デザインの修正
2022-07-14 [add]readmeの更新
2022-08-06 Update LICENSE
2022-09-28 markdownの更新
2022-09-28 markdownの更新2
2022-12-21 XT60PWコネクタに変えた
2022-12-22 トランシーバ選定途中、XT60PW
2022-12-23 CANトランシーバの選定(クリスマスイブですよ？（笑）)
2022-12-25 CAN周りの配線など
2022-12-26 レギュレータの追加など
2022-12-27 5Vレギュレータの追加など
2022-12-28 理想ダイオード回路(ディスクリート)の追加
2022-12-29 5VDCDCのMLCC選定、電源回りの整理
2022-12-30 5VDCDCの出力コンをOSコンにした
2022-12-30 +5V周りの冗長性を高める回路を構成(大晦日ですよ？（笑）)
2023-01-05 CANコントローラのXtal選定
2023-01-05 トランシーバ部分の設計終わり(仮)
2023-01-06 STM32の電源回り
2023-01-08 OSC周り
2023-01-09 DIPスイッチ周り
2023-01-14 RJ45の追加
2023-01-15 電流センサ周りの回路
2023-02-10 電源制御系周り
2023-02-11 ヒューズ選定
2023-02-14 kairozunoseiri
2023-02-17 DGND未選別のところまで
2023-02-19 develop_v2
2023-03-07 2023/03/07 信号ラインの配線途中
2023-03-08 2023/03/08 sintyoku
2023-03-09 2023/03/09進捗分
2023-03-10 2023/03/10の進捗
2023-03-20 2023/03/20の進捗
2023-03-21 2023/03/21の進捗
2023-03-23 2023/03/23 配線終了
2023-03-23 DRC OK,before I move it KiCad.
2023-03-23 Kicadへの移行後
2023-03-24 3dmodel top
2023-03-25 シルク 裏面 2023/03/25進捗分
2023-03-26 2023/03/26途中(1)
2023-03-26 3Dモデル当て終了
2023-03-26 DRC完了
2023-03-27 2023/03/27 sintyoku
2023-03-30 JLCPCBロゴを追加
2023-03-30 基板微修正、JLCPCBロゴ追加
2023-04-05 微修正失敗(1.524mm)
2023-04-07 kansei 2
2023-05-13 rename-file
2023-05-23 [add]BOM
2023-05-23 [update]readme_BOM
2023-05-23 [update]readme.md
2023-05-23 LICENSE の更新
2023-05-30 [update
